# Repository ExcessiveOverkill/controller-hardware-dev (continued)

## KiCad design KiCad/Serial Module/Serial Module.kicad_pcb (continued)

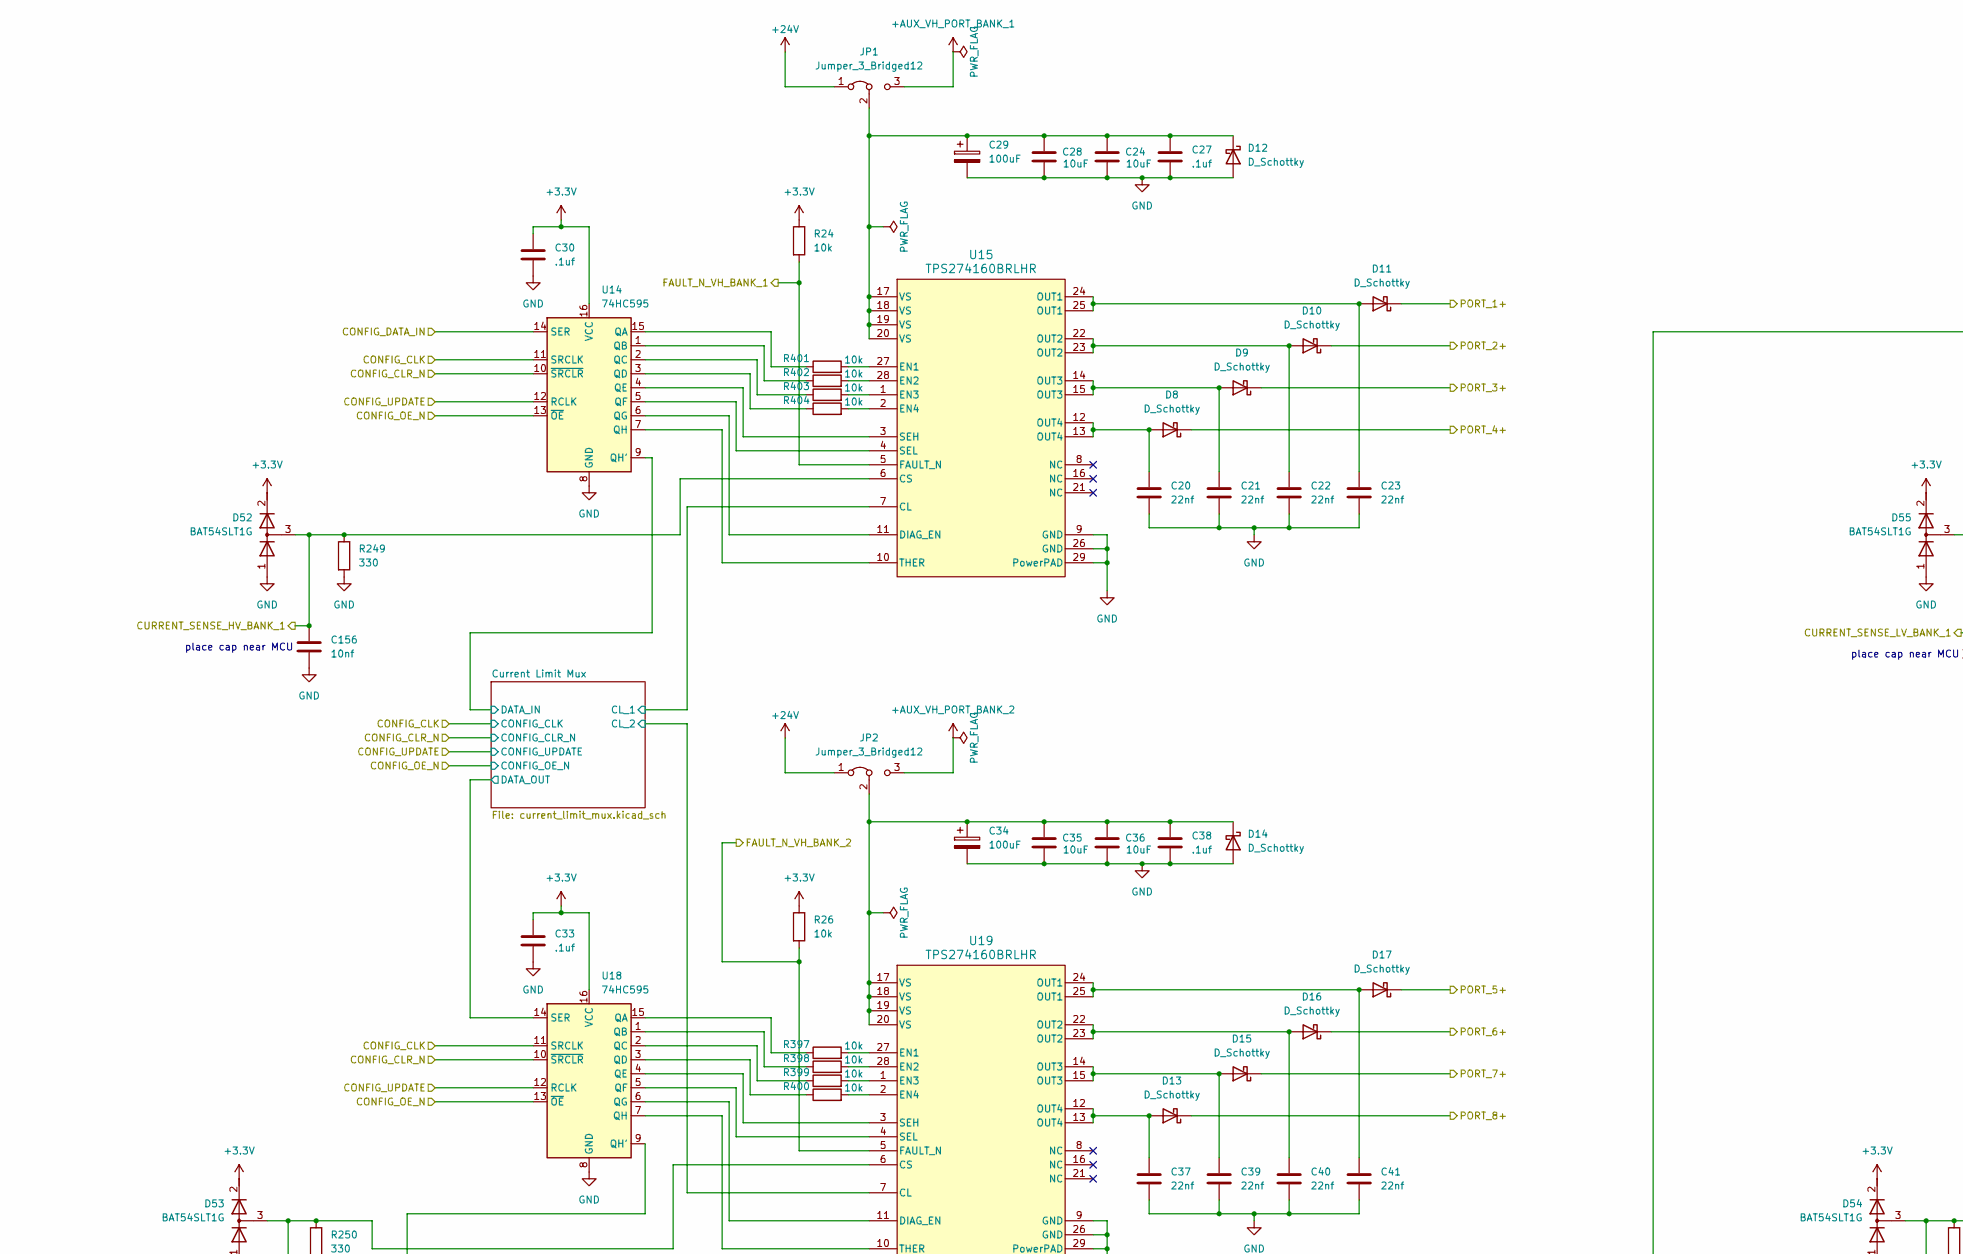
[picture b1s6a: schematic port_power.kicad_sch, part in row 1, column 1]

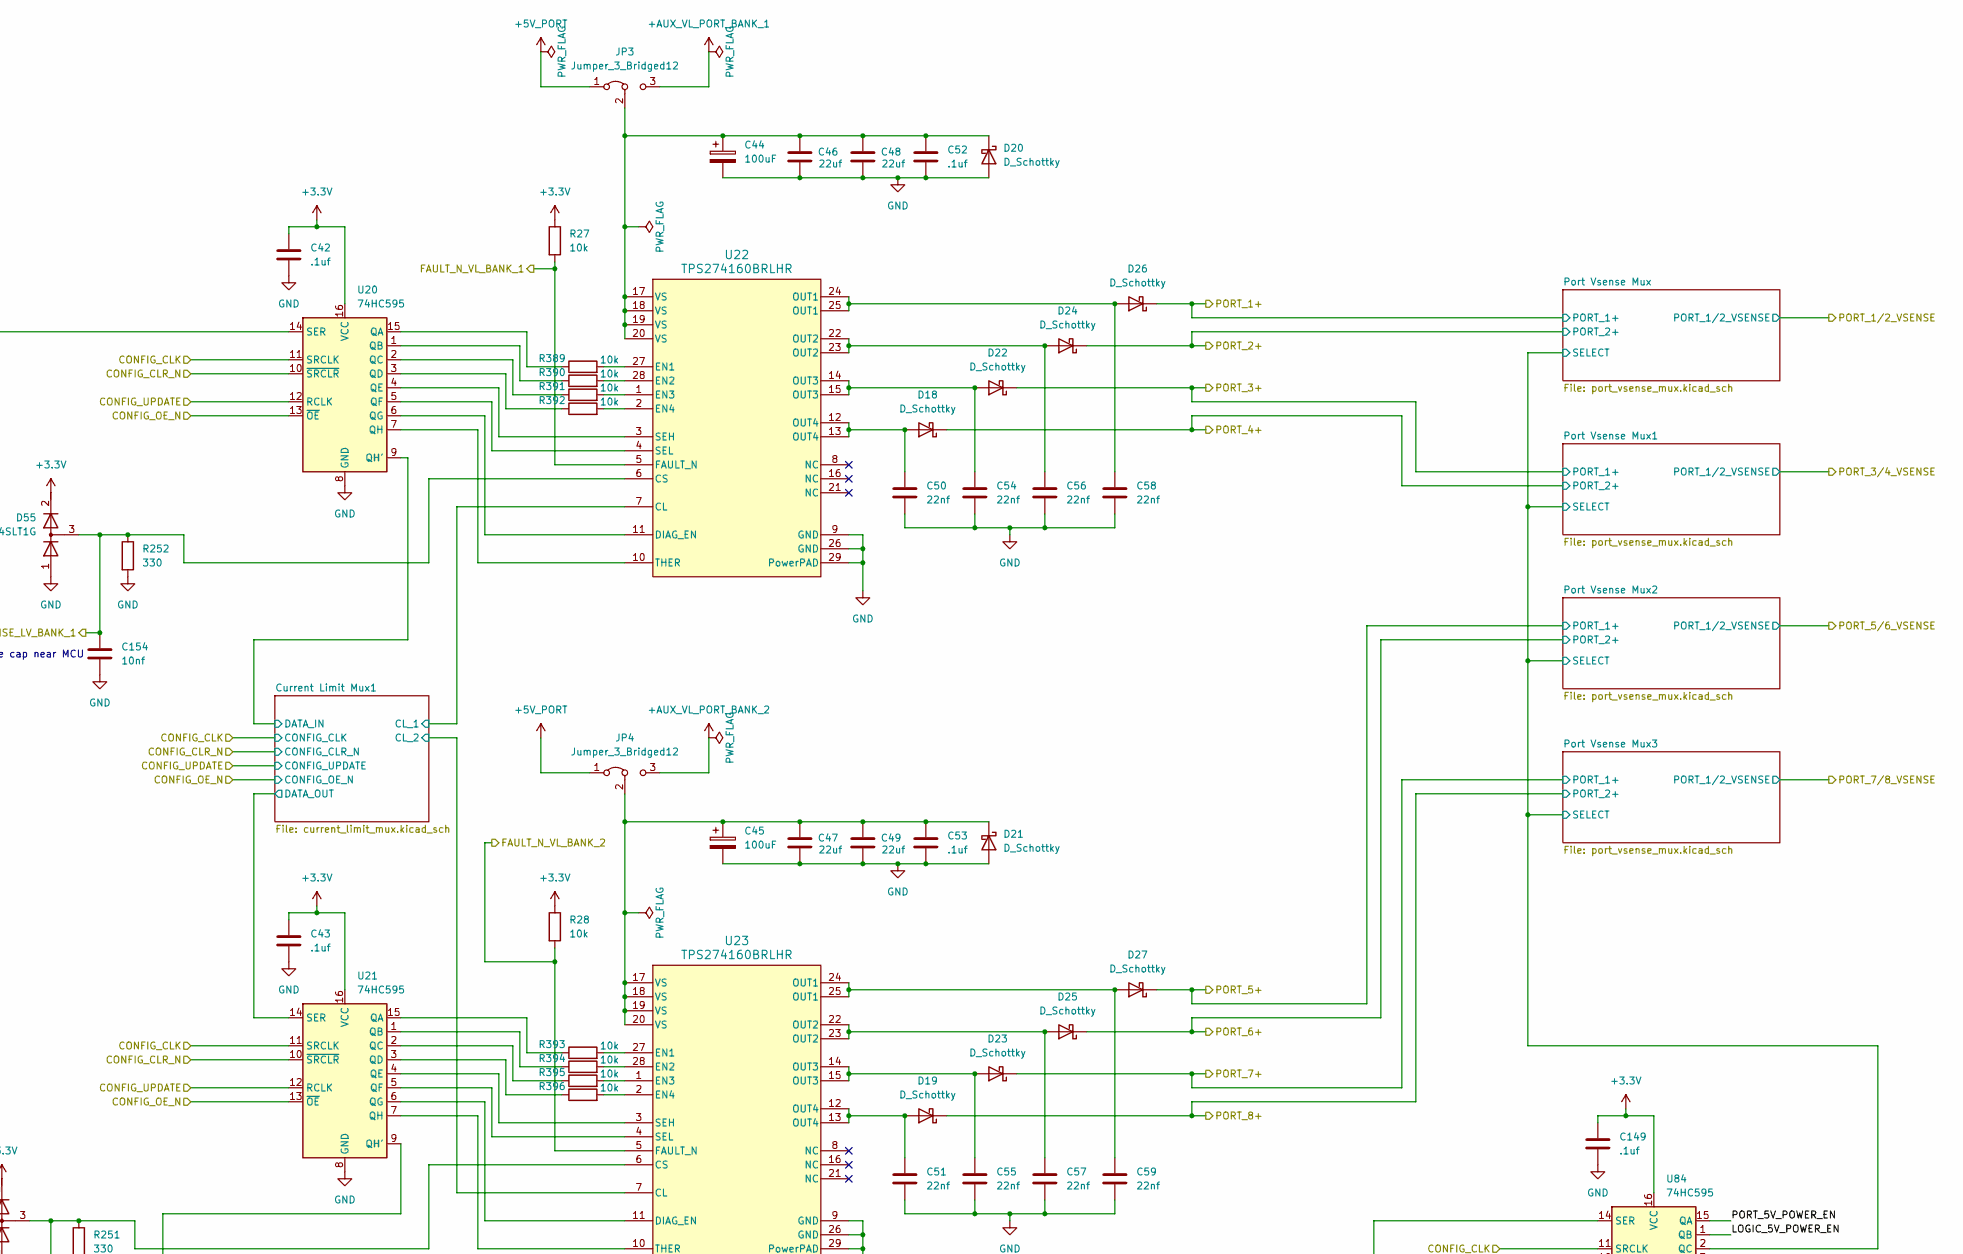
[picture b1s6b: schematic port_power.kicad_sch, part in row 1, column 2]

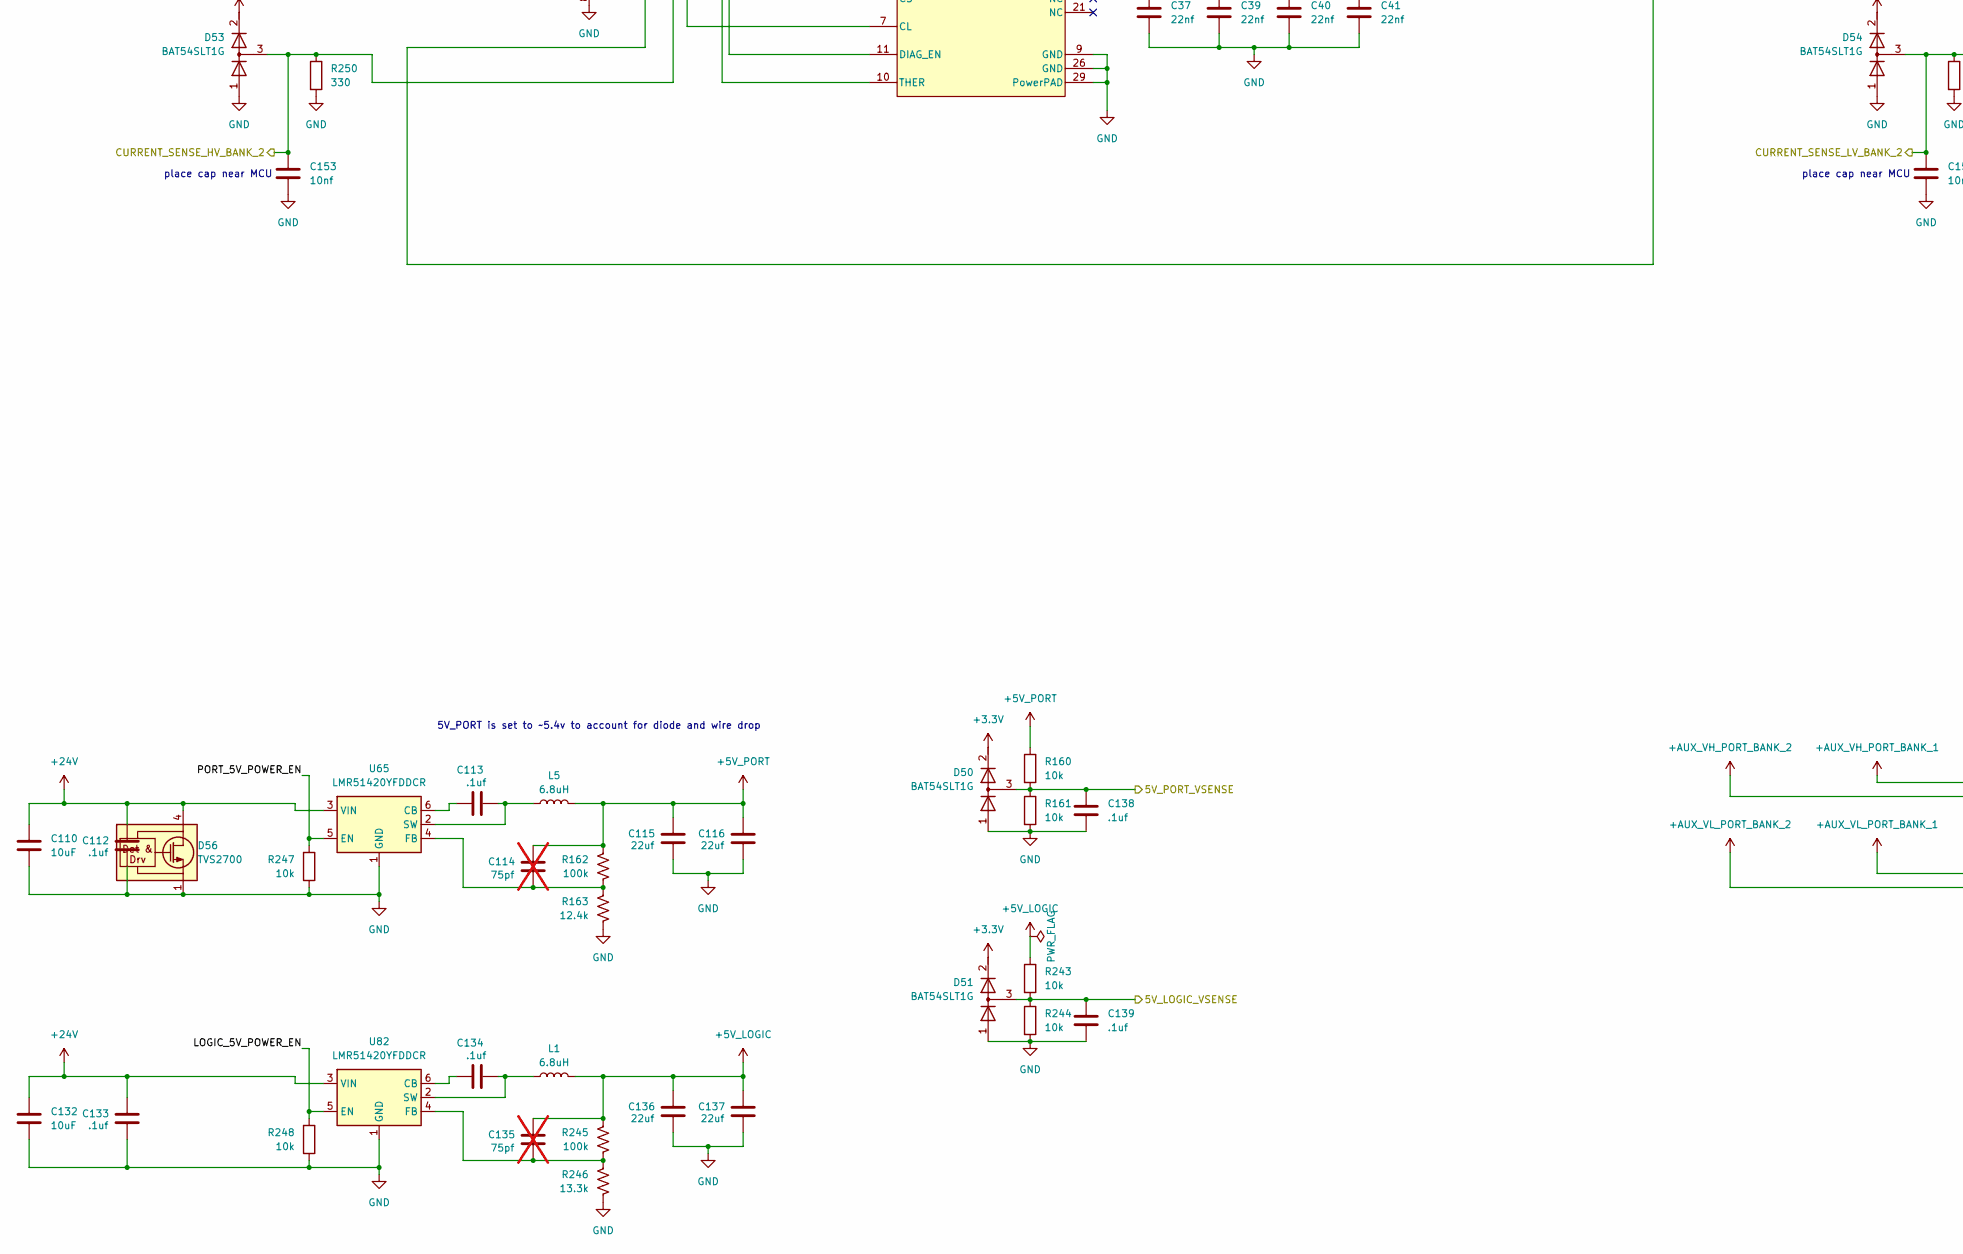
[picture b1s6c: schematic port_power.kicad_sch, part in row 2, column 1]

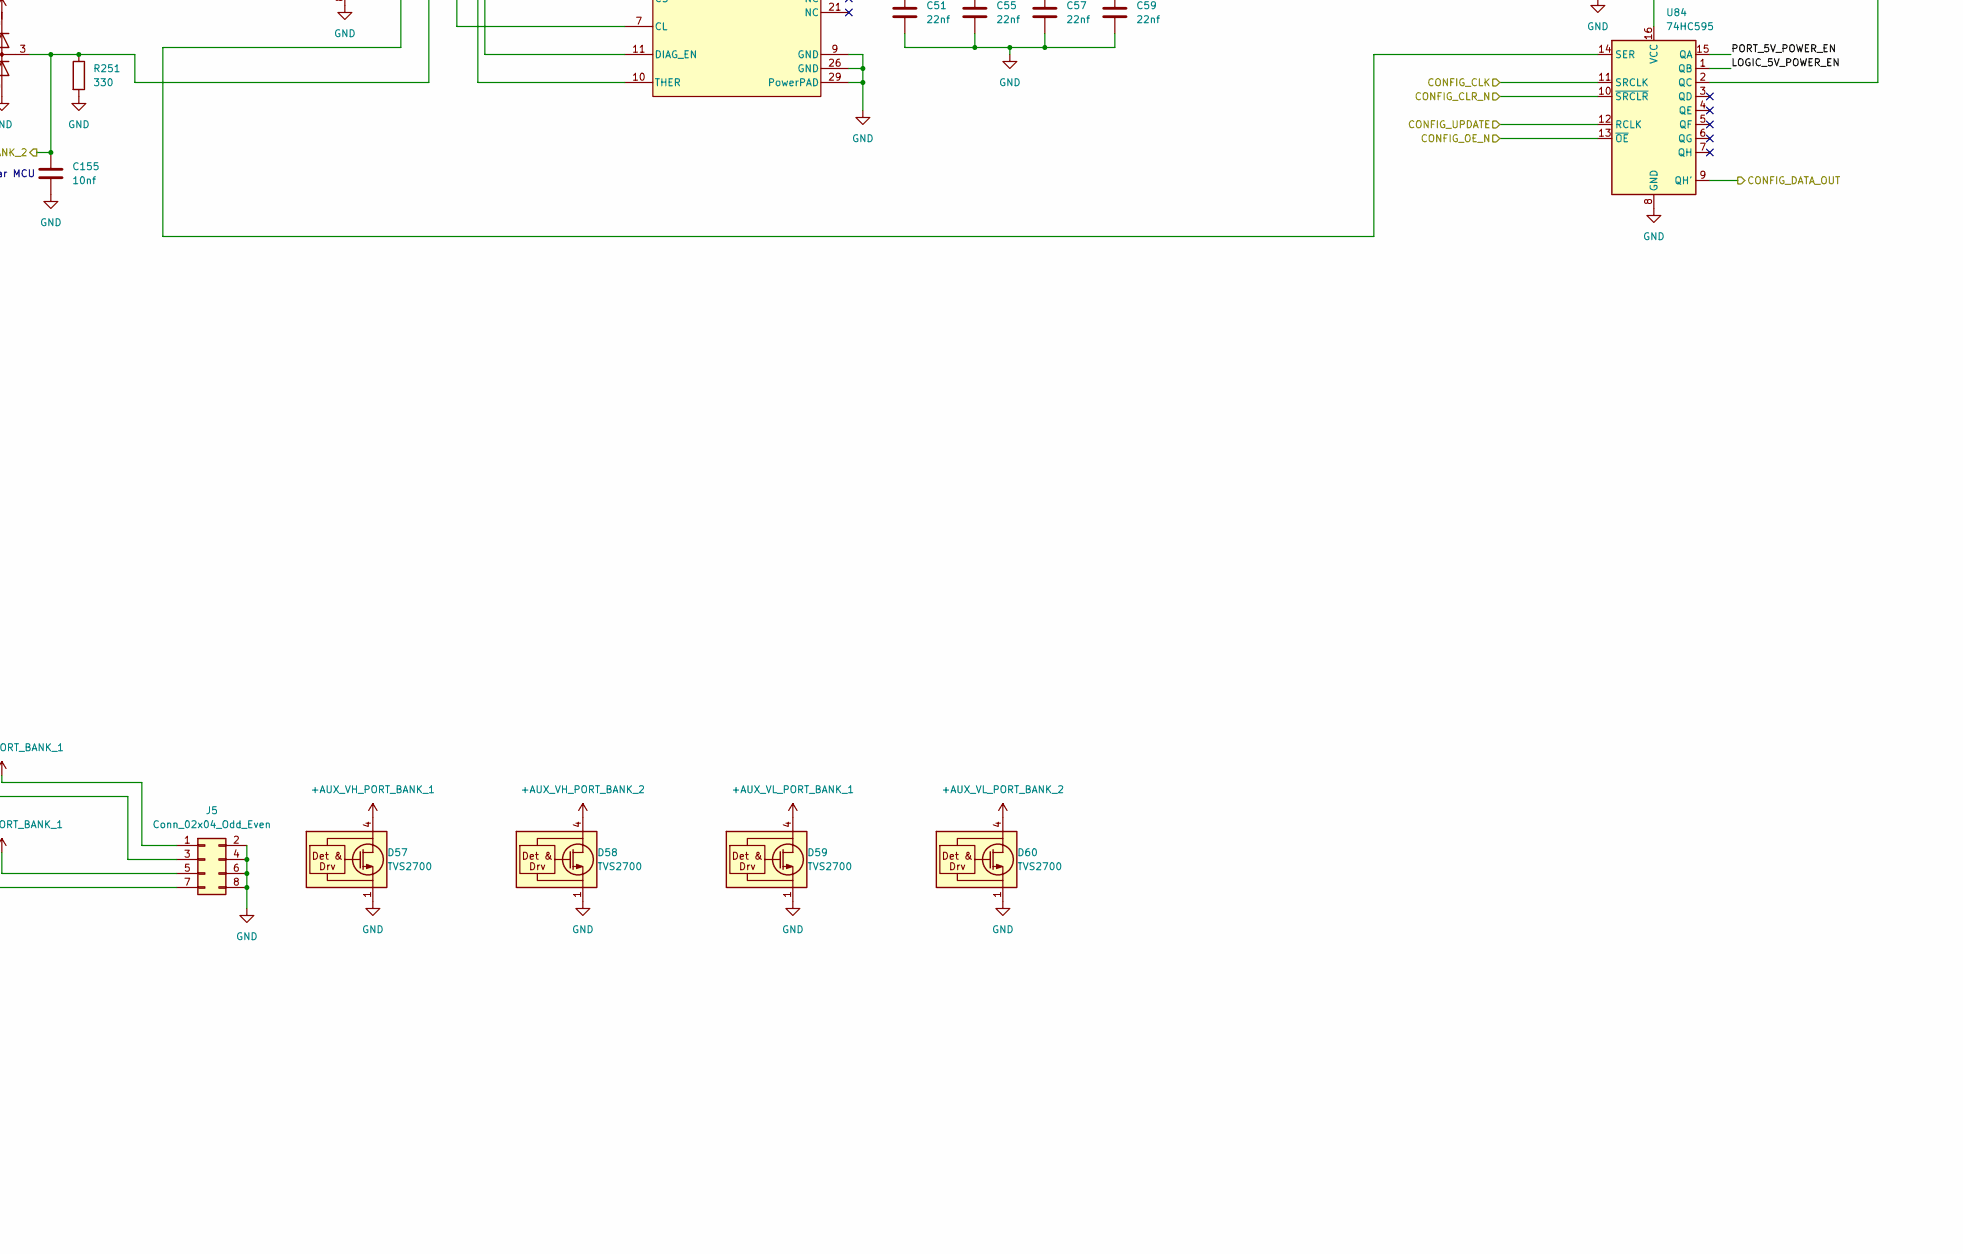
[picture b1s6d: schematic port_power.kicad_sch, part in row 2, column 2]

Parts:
C20, C21, C22, C23, C37, C39, C40, C41, C50, C51, C54, C55, C56, C57, C58, C59: 22nf; C_0402_1005Metric; Part number CC0402KRX7R9BB223; LCSC# C107026
C24, C28, C35, C36, C110, C132: 10uF; C_1210_3225Metric; Part number CC1210KKX7R9BB106; LCSC# C596319
C27, C30, C33, C38, C42, C43, C52, C53, C112, C113, C133, C134, C138, C139, C149: .1uf; C_0402_1005Metric; Part number CC0402KRX7R9BB104; LCSC# C131394
C29, C34, C44, C45: 100uF; CP_Elec_6.3x7.7; Part number JVJ50V100M6x8; LCSC# C46550415
C46, C47, C48, C49, C115, C116, C136, C137: 22uf; C_0805_2012Metric; Part number CC0805MKX5R8BB226; LCSC# C784585
C114, C135: 75pf; C_0402_1005Metric; Part number CC0402JRNPO9BN750; LCSC# C107010; not fitted
C153, C154, C155, C156: 10nf; C_0402_1005Metric; Part number CC0402KRX7R9BB103; LCSC# C60133
D8, D9, D10, D11, D12, D13, D14, D15, D16, D17, D18, D19, D20, D21, D22, D23, D24, D25, D26, D27: D_Schottky; D_SOD-123F; Part number K24; LCSC# C908664
D50, D51, D52, D53, D54, D55: BAT54SLT1G; SOT-23; Part number LBAT54SLT1G; LCSC# C12765
D56, D57, D58, D59, D60: TVS2700; WSON-6-1EP_2x2mm_P0.65mm_EP1x1.6mm; Part number TVS2700DRVR; LCSC# C523797
J5: Conn_02x04_Odd_Even; 2x04_P3.5_KF2EDGSR; Part number KF2EDGSR-3.5-2*4P; LCSC# C2923262
JP1, JP2, JP3, JP4: Jumper_3_Bridged12; PinHeader_1x03_P2.54mm_Horizontal_Stacked_Shunt12; Part number PZ254V-11-03P; LCSC# C2937625
L1, L5: 6.8uH; L_Changjiang_FXL0650; Part number FXL0650-6R8-M; LCSC# C475530
R24, R26, R27, R28, R160, R161, R243, R244, R247, R248, R389, R390, R391, R392, R393, R394, R395, R396, R397, R398, R399, R400, R401, R402, R403, R404: 10k; R_0402_1005Metric; Part number RC0402FR-0710KL; LCSC# C60490
R162, R245: 100k; R_0402_1005Metric; Part number RC0402FR-07100KL; LCSC# C60491
R163: 12.4k; R_0402_1005Metric; Part number RC0402FR-0712K4L; LCSC# C138060
R246: 13.3k; R_0402_1005Metric; Part number RC0402FR-0713K3L; LCSC# C274352
R249, R250, R251, R252: 330; R_0402_1005Metric; Part number RC0402FR-07330RL; LCSC# C105875
U14, U18, U20, U21, U84: 74HC595; DHVQFN-16-1EP_2.5x3.5mm_P0.5mm_EP1x2mm; Part number 74HC595BQ,115; LCSC# C730243
U15, U19, U22, U23: TPS274160BRLHR; VQFN-28-1EP_4x5mm_P0.5mm_EP2.55x3.55mm_ThermalVias; Part number TPS274160BRLHR; LCSC# C2797257
U65, U82: LMR51420YFDDCR; SOT-23-6; Part number LMR51420YFDDCR; LCSC# C7296200

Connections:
+3.3V: C30.1, C33.1, C42.1, C43.1, C149.1, D50.2 (K), D51.2 (K), D52.2 (K), D53.2 (K), D54.2 (K), D55.2 (K), R24.1, R26.1, R27.1, R28.1, U14.16 (VCC), U18.16 (VCC), U20.16 (VCC), U21.16 (VCC), U84.16 (VCC); also elsewhere on the board
+5V_LOGIC: C135.2, C136.2, C137.2, L1.2, R243.1, R245.2; also elsewhere on the board
+5V_PORT: C114.2, C115.2, C116.2, JP3.1 (A), JP4.1 (A), L5.2, R160.1, R162.2
+24V: C110.1, C112.2, C132.1, C133.2, D56.4 (IN), D56.5 (IN), D56.6 (IN), JP1.1 (A), JP2.1 (A), U65.3 (VIN), U82.3 (VIN); also elsewhere on the board
+AUX_VH_PORT_BANK_1: D57.4 (IN), D57.5 (IN), D57.6 (IN), J5.1, JP1.3 (B)
+AUX_VH_PORT_BANK_2: D58.4 (IN), D58.5 (IN), D58.6 (IN), J5.3, JP2.3 (B)
+AUX_VL_PORT_BANK_1: D59.4 (IN), D59.5 (IN), D59.6 (IN), J5.5, JP3.3 (B)
+AUX_VL_PORT_BANK_2: D60.4 (IN), D60.5 (IN), D60.6 (IN), J5.7, JP4.3 (B)
/MCU/5V_LOGIC_SENSE: C139.1, D51.3 (common), R243.2, R244.1; also elsewhere on the board
/MCU/5V_PORT_SENSE: C138.1, D50.3 (common), R160.2, R161.1; also elsewhere on the board
/MCU/CONFIG_CLK: U14.11 (SRCLK), U18.11 (SRCLK), U20.11 (SRCLK), U21.11 (SRCLK), U84.11 (SRCLK); also elsewhere on the board
/MCU/CONFIG_CLR_N: U14.10 (~SRCLR), U18.10 (~SRCLR), U20.10 (~SRCLR), U21.10 (~SRCLR), U84.10 (~SRCLR); also elsewhere on the board
/MCU/CONFIG_OE_N: U14.13 (~OE), U18.13 (~OE), U20.13 (~OE), U21.13 (~OE), U84.13 (~OE); also elsewhere on the board
/MCU/CONFIG_UPDATE: U14.12 (RCLK), U18.12 (RCLK), U20.12 (RCLK), U21.12 (RCLK), U84.12 (RCLK); also elsewhere on the board
/MCU/FAULT_N_HV_BANK_1: R24.2, U15.5 (FAULT_N); also elsewhere on the board
/MCU/FAULT_N_HV_BANK_2: R26.2, U19.5 (FAULT_N); also elsewhere on the board
/MCU/FAULT_N_LV_BANK_1: R27.2, U22.5 (FAULT_N); also elsewhere on the board
/MCU/FAULT_N_LV_BANK_2: R28.2, U23.5 (FAULT_N); also elsewhere on the board
/MCU/HV_BANK_1_CURRENT_SENSE: C156.1, D52.3 (common), R249.1, U15.6 (CS); also elsewhere on the board
/MCU/HV_BANK_2_CURRENT_SENSE: C153.1, D53.3 (common), R250.1, U19.6 (CS); also elsewhere on the board
/MCU/LV_BANK_1_CURRENT_SENSE: C154.1, D55.3 (common), R252.1, U22.6 (CS); also elsewhere on the board
/MCU/LV_BANK_2_CURRENT_SENSE: C155.1, D54.3 (common), R251.1, U23.6 (CS); also elsewhere on the board
/Transceivers/LED_SER_3V3: U84.9 (QH'); also elsewhere on the board
/Transceivers/PORT_1+: D11.1 (K), D26.1 (K); also elsewhere on the board
/Transceivers/PORT_2+: D10.1 (K), D24.1 (K); also elsewhere on the board
/Transceivers/PORT_3+: D9.1 (K), D22.1 (K); also elsewhere on the board
/Transceivers/PORT_4+: D8.1 (K), D18.1 (K); also elsewhere on the board
/Transceivers/PORT_5+: D17.1 (K), D27.1 (K); also elsewhere on the board
/Transceivers/PORT_6+: D16.1 (K), D25.1 (K); also elsewhere on the board
/Transceivers/PORT_7+: D15.1 (K), D23.1 (K); also elsewhere on the board
/Transceivers/PORT_8+: D13.1 (K), D19.1 (K); also elsewhere on the board
/Transceivers/Port Power/CONFIG_DATA_IN: U14.14 (SER); also elsewhere on the board
/Transceivers/Port Power/Current Limit Mux1/CL_1: U22.7 (CL); also elsewhere on the board
/Transceivers/Port Power/Current Limit Mux1/CL_2: U23.7 (CL); also elsewhere on the board
/Transceivers/Port Power/Current Limit Mux1/DATA_IN: U20.9 (QH'); also elsewhere on the board
/Transceivers/Port Power/Current Limit Mux1/DATA_OUT: U21.14 (SER); also elsewhere on the board
/Transceivers/Port Power/Current Limit Mux/CL_1: U15.7 (CL); also elsewhere on the board
/Transceivers/Port Power/Current Limit Mux/CL_2: U19.7 (CL); also elsewhere on the board
/Transceivers/Port Power/Current Limit Mux/DATA_IN: U14.9 (QH'); also elsewhere on the board
/Transceivers/Port Power/Current Limit Mux/DATA_OUT: U18.14 (SER); also elsewhere on the board
/Transceivers/Port Power/LOGIC_5V_POWER_EN: R248.2, U82.5 (EN), U84.1 (QB)
/Transceivers/Port Power/PORT_5V_POWER_EN: R247.2, U65.5 (EN), U84.15 (QA)
/Transceivers/Port Power/Port Vsense Mux/SELECT: U84.2 (QC); also elsewhere on the board
GND: C20.2, C21.2, C22.2, C23.2, C24.1, C27.2, C28.1, C29.2, C30.2, C33.2, C34.2, C35.1, C36.1, C37.2, C38.2, C39.2, C40.2, C41.2, C42.2, C43.2, C44.2, C45.2, C46.1, C47.1, C48.1, C49.1, C50.2, C51.2, C52.2, C53.2, C54.2, C55.2, C56.2, C57.2, C58.2, C59.2, C110.2, C112.1, C115.1, C116.1, C132.2, C133.1, C136.1, C137.1, C138.2, C139.2, C149.2, C153.2, C154.2, C155.2, C156.2, D12.2 (A), D14.2 (A), D20.2 (A), D21.2 (A), D50.1 (A), D51.1 (A), D52.1 (A), D53.1 (A), D54.1 (A), D55.1 (A), D56.1 (GND), D56.2 (GND), D56.3 (GND), D56.7 (GND), D57.1 (GND), D57.2 (GND), D57.3 (GND), D57.7 (GND), D58.1 (GND), D58.2 (GND), D58.3 (GND), D58.7 (GND), D59.1 (GND), D59.2 (GND), D59.3 (GND), D59.7 (GND), D60.1 (GND), D60.2 (GND), D60.3 (GND), D60.7 (GND), J5.2, J5.4, J5.6, J5.8, R161.2, R163.1, R244.2, R246.1, R247.1, R248.1, R249.2, R250.2, R251.2, R252.2, U14.8 (GND), U15.9 (GND), U15.26 (GND), U15.29 (PowerPAD), U18.8 (GND), U19.9 (GND), U19.26 (GND), U19.29 (PowerPAD), U20.8 (GND), U21.8 (GND), U22.9 (GND), U22.26 (GND), U22.29 (PowerPAD), U23.9 (GND), U23.26 (GND), U23.29 (PowerPAD), U65.1 (GND), U82.1 (GND), U84.8 (GND); also elsewhere on the board
unnamed: C20.1, D8.2 (A), U15.12 (OUT4), U15.13 (OUT4)
unnamed: C21.1, D9.2 (A), U15.14 (OUT3), U15.15 (OUT3)
unnamed: C22.1, D10.2 (A), U15.22 (OUT2), U15.23 (OUT2)
unnamed: C23.1, D11.2 (A), U15.24 (OUT1), U15.25 (OUT1)
unnamed: C24.2, C27.1, C28.2, C29.1, D12.1 (K), JP1.2 (C), U15.17 (VS), U15.18 (VS), U15.19 (VS), U15.20 (VS)
unnamed: C37.1, D13.2 (A), U19.12 (OUT4), U19.13 (OUT4)
unnamed: C34.1, C35.2, C36.2, C38.1, D14.1 (K), JP2.2 (C), U19.17 (VS), U19.18 (VS), U19.19 (VS), U19.20 (VS)
unnamed: C39.1, D15.2 (A), U19.14 (OUT3), U19.15 (OUT3)
unnamed: C40.1, D16.2 (A), U19.22 (OUT2), U19.23 (OUT2)
unnamed: C41.1, D17.2 (A), U19.24 (OUT1), U19.25 (OUT1)
unnamed: C50.1, D18.2 (A), U22.12 (OUT4), U22.13 (OUT4)
unnamed: C51.1, D19.2 (A), U23.12 (OUT4), U23.13 (OUT4)
unnamed: C44.1, C46.2, C48.2, C52.1, D20.1 (K), JP3.2 (C), U22.17 (VS), U22.18 (VS), U22.19 (VS), U22.20 (VS)
unnamed: C45.1, C47.2, C49.2, C53.1, D21.1 (K), JP4.2 (C), U23.17 (VS), U23.18 (VS), U23.19 (VS), U23.20 (VS)
unnamed: C54.1, D22.2 (A), U22.14 (OUT3), U22.15 (OUT3)
unnamed: C55.1, D23.2 (A), U23.14 (OUT3), U23.15 (OUT3)
unnamed: C56.1, D24.2 (A), U22.22 (OUT2), U22.23 (OUT2)
unnamed: C57.1, D25.2 (A), U23.22 (OUT2), U23.23 (OUT2)
unnamed: C58.1, D26.2 (A), U22.24 (OUT1), U22.25 (OUT1)
unnamed: C59.1, D27.2 (A), U23.24 (OUT1), U23.25 (OUT1)
unnamed: R401.1, U14.15 (QA)
unnamed: R402.1, U14.1 (QB)
unnamed: R403.1, U14.2 (QC)
unnamed: R404.1, U14.3 (QD)
unnamed: U14.4 (QE), U15.3 (SEH)
unnamed: U14.5 (QF), U15.4 (SEL)
unnamed: U14.6 (QG), U15.11 (DIAG_EN)
unnamed: U14.7 (QH), U15.10 (THER)
unnamed: R401.2, U15.27 (EN1)
unnamed: R402.2, U15.28 (EN2)
unnamed: R403.2, U15.1 (EN3)
unnamed: R404.2, U15.2 (EN4)
unnamed: R397.1, U18.15 (QA)
unnamed: R398.1, U18.1 (QB)
unnamed: R399.1, U18.2 (QC)
unnamed: R400.1, U18.3 (QD)
unnamed: U18.4 (QE), U19.3 (SEH)
unnamed: U18.5 (QF), U19.4 (SEL)
unnamed: U18.6 (QG), U19.11 (DIAG_EN)
unnamed: U18.9 (QH'), U20.14 (SER)
unnamed: U18.7 (QH), U19.10 (THER)
unnamed: R397.2, U19.27 (EN1)
unnamed: R398.2, U19.28 (EN2)
unnamed: R399.2, U19.1 (EN3)
unnamed: R400.2, U19.2 (EN4)
unnamed: R389.1, U20.15 (QA)
unnamed: R390.1, U20.1 (QB)
unnamed: R391.1, U20.2 (QC)
unnamed: R392.1, U20.3 (QD)
unnamed: U20.4 (QE), U22.3 (SEH)
unnamed: U20.5 (QF), U22.4 (SEL)
unnamed: U20.6 (QG), U22.11 (DIAG_EN)
unnamed: U20.7 (QH), U22.10 (THER)
unnamed: R393.1, U21.15 (QA)
unnamed: R394.1, U21.1 (QB)
unnamed: R395.1, U21.2 (QC)
unnamed: R396.1, U21.3 (QD)
unnamed: U21.4 (QE), U23.3 (SEH)
unnamed: U21.5 (QF), U23.4 (SEL)
unnamed: U21.6 (QG), U23.11 (DIAG_EN)
unnamed: U21.9 (QH'), U84.14 (SER)
unnamed: U21.7 (QH), U23.10 (THER)
unnamed: R389.2, U22.27 (EN1)
unnamed: R390.2, U22.28 (EN2)
unnamed: R391.2, U22.1 (EN3)
unnamed: R392.2, U22.2 (EN4)
unnamed: R393.2, U23.27 (EN1)
unnamed: R394.2, U23.28 (EN2)
unnamed: R395.2, U23.1 (EN3)
unnamed: R396.2, U23.2 (EN4)
unnamed: C113.1, U65.6 (CB)
unnamed: C114.1, R162.1, R163.2, U65.4 (FB)
unnamed: C113.2, L5.1, U65.2 (SW)
unnamed: C134.1, U82.6 (CB)
unnamed: C135.1, R245.1, R246.2, U82.4 (FB)
unnamed: C134.2, L1.1, U82.2 (SW)

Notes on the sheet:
place cap near MCU
5V_PORT is set to ~5.4v to account for diode and wire drop

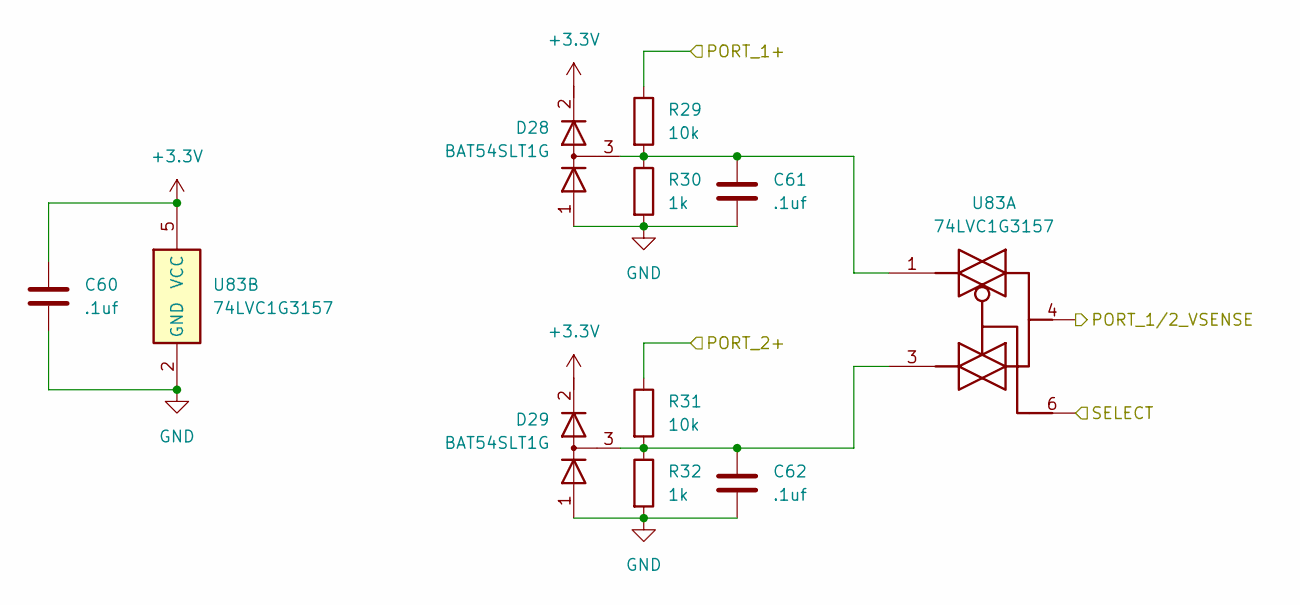
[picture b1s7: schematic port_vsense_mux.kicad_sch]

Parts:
C60, C61, C62: .1uf; C_0402_1005Metric; Part number CC0402KRX7R9BB104; LCSC# C131394
D28, D29: BAT54SLT1G; SOT-23; Part number LBAT54SLT1G; LCSC# C12765
R29, R31: 10k; R_0402_1005Metric; Part number RC0402FR-0710KL; LCSC# C60490
R30, R32: 1k; R_0402_1005Metric; Part number RC0402FR-071KL; LCSC# C106235
U83: 74LVC1G3157; SOT-363_SC-70-6; Part number SN74LVC1G3157DCKR; LCSC# C38663

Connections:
+3.3V: C60.1, D28.2 (K), D29.2 (K), U83.5 (VCC); also elsewhere on the board
/MCU/PORT_1/2_VSENSE: U83.4; also elsewhere on the board
/Transceivers/PORT_1+: R29.1; also elsewhere on the board
/Transceivers/PORT_2+: R31.1; also elsewhere on the board
/Transceivers/Port Power/Port Vsense Mux/SELECT: U83.6; also elsewhere on the board
GND: C60.2, C61.2, C62.2, D28.1 (A), D29.1 (A), R30.2, R32.2, U83.2 (GND); also elsewhere on the board
unnamed: C61.1, D28.3 (common), R29.2, R30.1, U83.1
unnamed: C62.1, D29.3 (common), R31.2, R32.1, U83.3

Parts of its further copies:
C63, C64, C65, C66, C67, C148, C150, C151, C152: .1uf; C_0402_1005Metric; Part number CC0402KRX7R9BB104; LCSC# C131394
D30, D31, D32, D33, D34, D35: BAT54SLT1G; SOT-23; Part number LBAT54SLT1G; LCSC# C12765
R33, R35, R37, R39, R41, R43: 10k; R_0402_1005Metric; Part number RC0402FR-0710KL; LCSC# C60490
R34, R36, R38, R40, R42, R44: 1k; R_0402_1005Metric; Part number RC0402FR-071KL; LCSC# C106235
U85, U86, U87: 74LVC1G3157; SOT-363_SC-70-6; Part number SN74LVC1G3157DCKR; LCSC# C38663

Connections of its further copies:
+3.3V: C63.1, C66.1, C150.1, D30.2 (K), D31.2 (K), D32.2 (K), D33.2 (K), D34.2 (K), D35.2 (K), U85.5 (VCC), U86.5 (VCC), U87.5 (VCC); also elsewhere on the board
/MCU/PORT_3/4_VSENSE: U85.4; also elsewhere on the board
/MCU/PORT_5/6_VSENSE: U86.4; also elsewhere on the board
/MCU/PORT_7/8_VSENSE: U87.4; also elsewhere on the board
/Transceivers/PORT_3+: R33.1; also elsewhere on the board
/Transceivers/PORT_4+: R35.1; also elsewhere on the board
/Transceivers/PORT_5+: R37.1; also elsewhere on the board
/Transceivers/PORT_6+: R39.1; also elsewhere on the board
/Transceivers/PORT_7+: R41.1; also elsewhere on the board
/Transceivers/PORT_8+: R43.1; also elsewhere on the board
/Transceivers/Port Power/Port Vsense Mux/SELECT: U85.6, U86.6, U87.6; also elsewhere on the board
GND: C63.2, C64.2, C65.2, C66.2, C67.2, C148.2, C150.2, C151.2, C152.2, D30.1 (A), D31.1 (A), D32.1 (A), D33.1 (A), D34.1 (A), D35.1 (A), R34.2, R36.2, R38.2, R40.2, R42.2, R44.2, U85.2 (GND), U86.2 (GND), U87.2 (GND); also elsewhere on the board
unnamed: C64.1, D30.3 (common), R33.2, R34.1, U85.1
unnamed: C65.1, D31.3 (common), R35.2, R36.1, U85.3
unnamed: C67.1, D32.3 (common), R37.2, R38.1, U86.1
unnamed: C148.1, D33.3 (common), R39.2, R40.1, U86.3
unnamed: C151.1, D34.3 (common), R41.2, R42.1, U87.1
unnamed: C152.1, D35.3 (common), R43.2, R44.1, U87.3

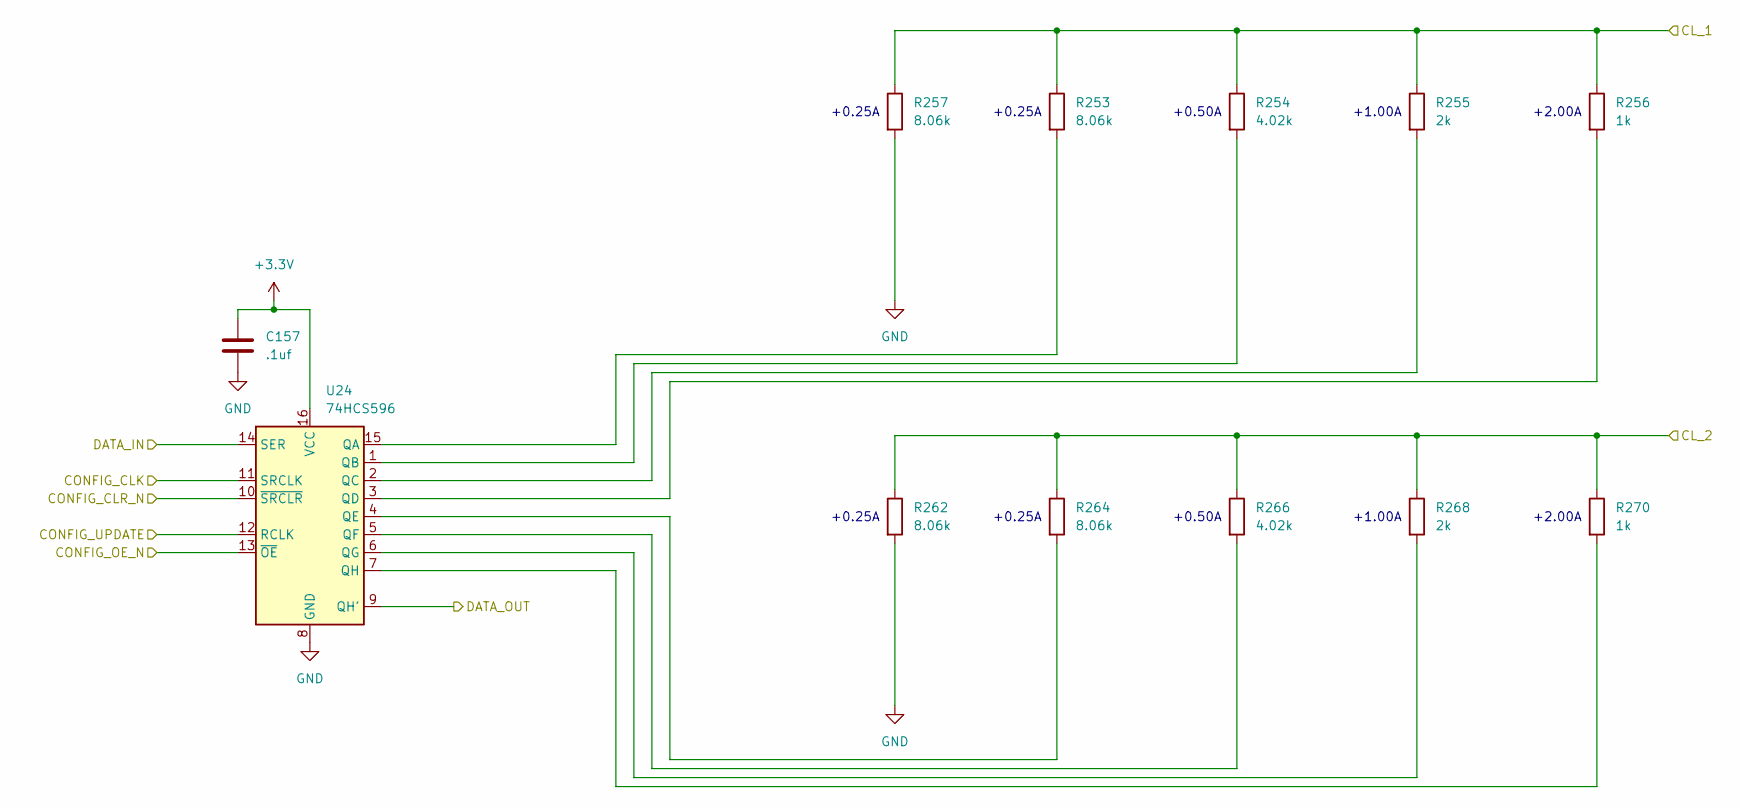
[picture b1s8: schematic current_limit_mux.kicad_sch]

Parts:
C157: .1uf; C_0402_1005Metric; Part number CC0402KRX7R9BB104; LCSC# C131394
R253, R257, R262, R264: 8.06k; R_0402_1005Metric; Part number RC0402FR-078K06L; LCSC# C276278
R254, R266: 4.02k; R_0402_1005Metric; Part number RC0402FR-074K02L; LCSC# C137968
R255, R268: 2k; R_0402_1005Metric; Part number RC0402FR-072KL; LCSC# C60488
R256, R270: 1k; R_0402_1005Metric; Part number RC0402FR-071KL; LCSC# C106235
U24: 74HCS596; TSSOP-16_4.4x5mm_P0.65mm; Part number SN74HCS596QPWRQ1; LCSC# C2862662

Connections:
+3.3V: C157.1, U24.16 (VCC); also elsewhere on the board
/MCU/CONFIG_CLK: U24.11 (SRCLK); also elsewhere on the board
/MCU/CONFIG_CLR_N: U24.10 (~SRCLR); also elsewhere on the board
/MCU/CONFIG_OE_N: U24.13 (~OE); also elsewhere on the board
/MCU/CONFIG_UPDATE: U24.12 (RCLK); also elsewhere on the board
/Transceivers/Port Power/Current Limit Mux/CL_1: R253.1, R254.1, R255.1, R256.1, R257.1; also elsewhere on the board
/Transceivers/Port Power/Current Limit Mux/CL_2: R262.1, R264.1, R266.1, R268.1, R270.1; also elsewhere on the board
/Transceivers/Port Power/Current Limit Mux/DATA_IN: U24.14 (SER); also elsewhere on the board
/Transceivers/Port Power/Current Limit Mux/DATA_OUT: U24.9 (QH'); also elsewhere on the board
GND: C157.2, R257.2, R262.2, U24.8 (GND); also elsewhere on the board
unnamed: R253.2, U24.15 (QA)
unnamed: R254.2, U24.1 (QB)
unnamed: R255.2, U24.2 (QC)
unnamed: R256.2, U24.3 (QD)
unnamed: R264.2, U24.4 (QE)
unnamed: R266.2, U24.5 (QF)
unnamed: R268.2, U24.6 (QG)
unnamed: R270.2, U24.7 (QH)

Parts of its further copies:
C158: .1uf; C_0402_1005Metric; Part number CC0402KRX7R9BB104; LCSC# C131394
R271, R272, R275, R276: 8.06k; R_0402_1005Metric; Part number RC0402FR-078K06L; LCSC# C276278
R279, R280: 4.02k; R_0402_1005Metric; Part number RC0402FR-074K02L; LCSC# C137968
R283, R284: 2k; R_0402_1005Metric; Part number RC0402FR-072KL; LCSC# C60488
R287, R288: 1k; R_0402_1005Metric; Part number RC0402FR-071KL; LCSC# C106235
U25: 74HCS596; TSSOP-16_4.4x5mm_P0.65mm; Part number SN74HCS596QPWRQ1; LCSC# C2862662

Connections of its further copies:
+3.3V: C158.1, U25.16 (VCC); also elsewhere on the board
/MCU/CONFIG_CLK: U25.11 (SRCLK); also elsewhere on the board
/MCU/CONFIG_CLR_N: U25.10 (~SRCLR); also elsewhere on the board
/MCU/CONFIG_OE_N: U25.13 (~OE); also elsewhere on the board
/MCU/CONFIG_UPDATE: U25.12 (RCLK); also elsewhere on the board
/Transceivers/Port Power/Current Limit Mux1/CL_1: R271.1, R275.1, R279.1, R283.1, R287.1; also elsewhere on the board
/Transceivers/Port Power/Current Limit Mux1/CL_2: R272.1, R276.1, R280.1, R284.1, R288.1; also elsewhere on the board
/Transceivers/Port Power/Current Limit Mux1/DATA_IN: U25.14 (SER); also elsewhere on the board
/Transceivers/Port Power/Current Limit Mux1/DATA_OUT: U25.9 (QH'); also elsewhere on the board
GND: C158.2, R271.2, R272.2, U25.8 (GND); also elsewhere on the board
unnamed: R275.2, U25.15 (QA)
unnamed: R279.2, U25.1 (QB)
unnamed: R283.2, U25.2 (QC)
unnamed: R287.2, U25.3 (QD)
unnamed: R276.2, U25.4 (QE)
unnamed: R280.2, U25.5 (QF)
unnamed: R284.2, U25.6 (QG)
unnamed: R288.2, U25.7 (QH)

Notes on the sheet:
+2.00A
+1.00A
+0.25A
+0.50A
